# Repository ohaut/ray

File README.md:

# Ray module

The ray module is a 3-channel LED controller, designed to be
small, and built on the OHAUT framework.

OHAUT framework provides the common web interface, WiFi management,
connectivity to other smart devices (like Alexa , homeassistant, etc..),
as well as an update system which allows firmware to be published on
this repository (see [the gh-pages branch](https://github.com/ohaut/ray/tree/gh-pages/firmware/master) ),
long term it probably makes more sense to release via github releases of binaries.

The firmware code for this device is available in the [firmware](./firmware) directory.

The hardware design for this devices is available in the [hardware](./hardware) directory.

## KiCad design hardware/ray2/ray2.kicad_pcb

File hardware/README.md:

# Hardware design

This directory contains the hardware designs for the ray component.
All the designs are made using KiCad which is free and opensource
software, you can download it here: [www.kicad.org](https://www.kicad.org/)

* ray2: Is the latest version of the design, based on the RISC-V esp32c3
  chip from espressif, with embedded 4MB flash.

* microdimmer: Is a small footprint version, based on ESP8266, using SMD
  components and a DC/DC regulator.

* base_prototype: This was the initial protpotype, based on ESP8266, using
  insertion components on a 2-layer PCB.

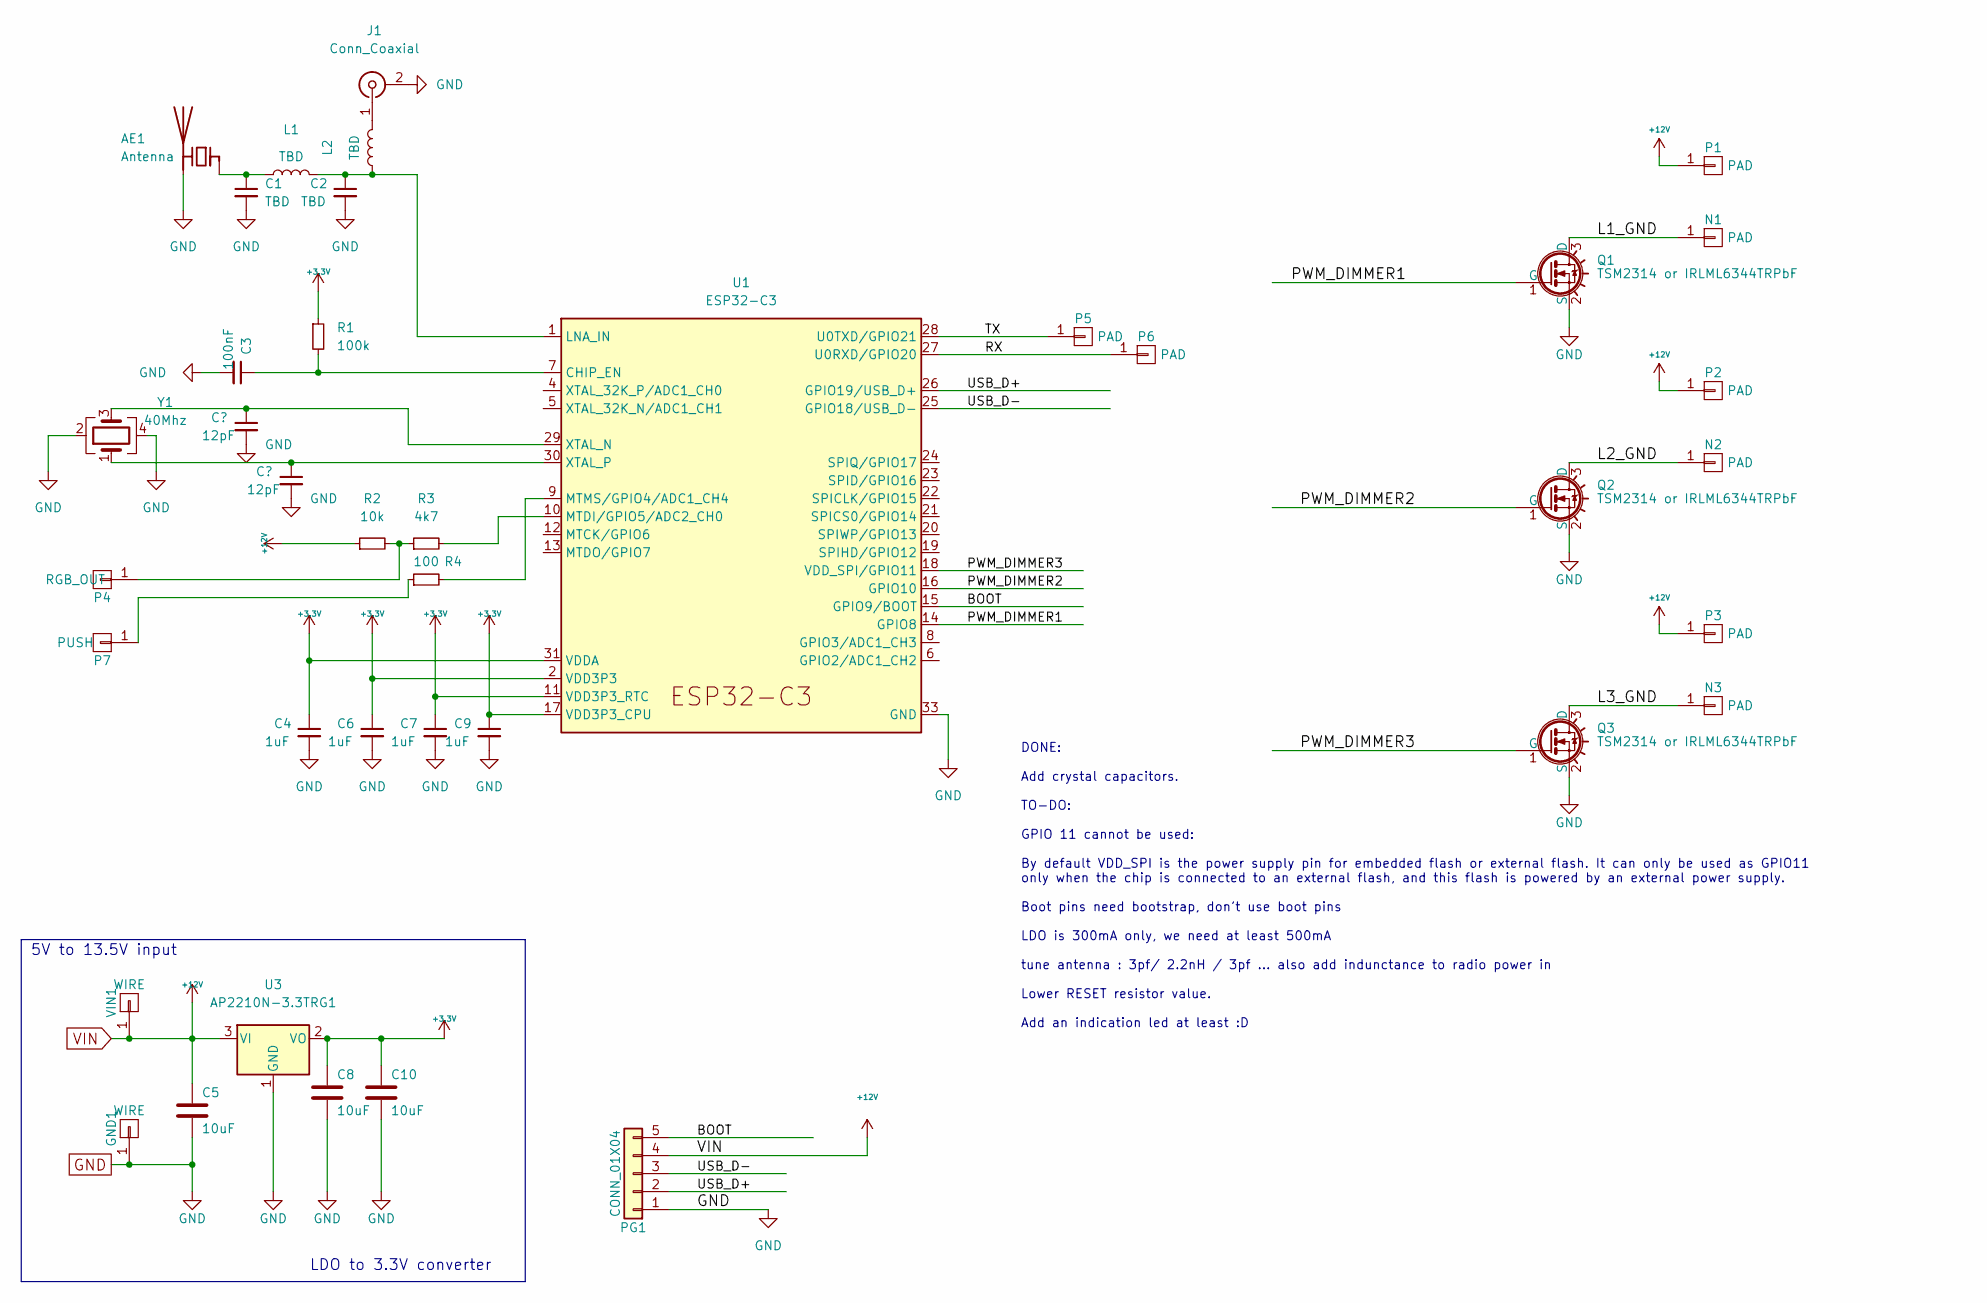
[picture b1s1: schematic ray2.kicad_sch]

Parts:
AE1: Antenna; Texas_SWRA117D_2.4GHz_Left
C1, C2: TBD; C_0402_1005Metric
C3: 100nF; C_0402_1005Metric
C4, C6, C7, C9: 1uF; C_0402_1005Metric
C5, C8, C10: 10uF; C_0603_1608Metric
GND1: WIRE; SolderWire-1.5sqmm_1x01_D1.7mm_OD3.9mm
J1: Conn_Coaxial; coaxial_u.fl-r-smt-1
L1, L2: TBD; L_0402_1005Metric
N1, N2, N3: PAD; SolderWire-0.5sqmm_1x01_D0.9mm_OD2.1mm
P1, P2, P3: PAD; SolderWire-0.5sqmm_1x01_D0.9mm_OD2.1mm
P4: RGB_OUT; SolderWire-0.5sqmm_1x01_D0.9mm_OD2.1mm
P5, P6: PAD; SolderWirePad_1x01_SMD_1x2mm
P7: PUSH; SolderWire-0.5sqmm_1x01_D0.9mm_OD2.1mm
PG1: CONN_01X04; PinHeader_1x05_P1.27mm_Vertical
Q1, Q2, Q3: TSM2314 or IRLML6344TRPbF; SOT-23
R1: 100k; R_0402_1005Metric
R2: 10k; R_0402_1005Metric
R3: 4k7; R_0402_1005Metric
R4: 100; R_0402_1005Metric
U1: ESP32-C3; QFN-32-1EP_5x5mm_P0.5mm_EP3.45x3.45mm
U3: AP2210N-3.3TRG1; SOT-23
VIN1: WIRE; SolderWire-1.5sqmm_1x01_D1.7mm_OD3.9mm
Y1: 40Mhz; Crystal_SMD_2520-4Pin_2.5x2.0mm

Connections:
+3V3: C4.1, C6.1, C7.1, C8.1, C9.1, C10.1, R1.1, U1.2 (VDD3P3), U1.3 (VDD3P3), U1.11 (VDD3P3_RTC), U1.17 (VDD3P3_CPU), U1.31 (VDDA), U1.32 (VDDA), U3.2 (VO)
/BOOT: PG1.5, U1.15 (GPIO9/BOOT)
/L1_GND: N1.1, Q1.3 (D)
/L2_GND: N2.1, Q2.3 (D)
/L3_GND: N3.1, Q3.3 (D)
/PWM_DIMMER1: Q1.1 (G), U1.14 (GPIO8)
/PWM_DIMMER2: Q2.1 (G), U1.16 (GPIO10)
/PWM_DIMMER3: Q3.1 (G), U1.18 (VDD_SPI/GPIO11)
/RX: P6.1, U1.27 (U0RXD/GPIO20)
/TX: P5.1, U1.28 (U0TXD/GPIO21)
/USB_D+: PG1.2, U1.26 (GPIO19/USB_D+)
/USB_D-: PG1.3, U1.25 (GPIO18/USB_D-)
GND: AE1.2 (PCB_Trace), C1.2, C2.2, C3.2, C4.2, C5.2, C6.2, C7.2, C8.2, C9.2, C10.2, GND1.1, J1.2 (Ext), PG1.1, Q1.2 (S), Q2.2 (S), Q3.2 (S), U1.33 (GND), U3.1 (GND), Y1.2, Y1.4
unnamed: AE1.1 (FEED), C1.1, L1.1
unnamed: C2.1, L1.2, L2.1, U1.1 (LNA_IN)
unnamed: C3.1, R1.2, U1.7 (CHIP_EN)
unnamed: J1.1 (In), L2.2
unnamed: P4.1, R2.2, R3.1
unnamed: P7.1, R4.1
unnamed: R3.2, U1.10 (MTDI/GPIO5/ADC2_CH0)
unnamed: R4.2, U1.9 (MTMS/GPIO4/ADC1_CH4)
unnamed: U1.29 (XTAL_N), Y1.3
unnamed: U1.30 (XTAL_P), Y1.1
VIN: C5.1, P1.1, P2.1, P3.1, PG1.4, R2.1, U3.3 (VI), VIN1.1

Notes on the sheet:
LDO to 3.3V converter
5V to 13.5V input
DONE: Add crystal capacitors. TO-DO: GPIO 11 cannot be used: By default VDD_SPI is the power supply pin for embedded flash or external flash. It can only be used as GPIO11 only when the chip is connected to an external flash, and this flash is powered by an external power supply. Boot pins need boo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

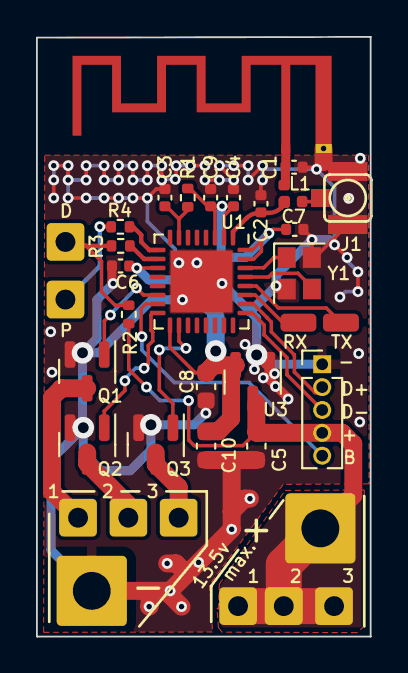
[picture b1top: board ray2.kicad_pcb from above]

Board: 2 copper layers, 18.5 x 33.3 mm, 37 parts (0 on the bottom side), 24 nets.

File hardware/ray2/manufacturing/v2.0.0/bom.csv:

"Id";"Designator";"Package";"Quantity";"Designation";"Supplier and ref";
1;"C10,C5,C8";"C_0603_1608Metric";3;"10uF";;;
2;"P2,P1,N3,N2,N1,P3";"SolderWire-0.5sqmm_1x01_D0.9mm_OD2.1mm";6;"PAD";;;
3;"R4";"R_0402_1005Metric";1;"100";;;
4;"C2,C1";"C_0402_1005Metric";2;"TBD";;;
5;"C7,C4,C6,C9";"C_0402_1005Metric";4;"1uF";;;
6;"Q1,Q2,Q3";"SOT-23";3;"TSM2314 or IRLML6344TRPbF";;;
7;"P6,P5";"SolderWirePad_1x01_SMD_1x2mm";2;"PAD";;;
8;"J1";"coaxial_u.fl-r-smt-1";1;"Conn_Coaxial";;;
9;"PG1";"PinHeader_1x05_P1.27mm_Vertical";1;"CONN_01X04";;;
10;"Y1";"Crystal_SMD_2520-4Pin_2.5x2.0mm";1;"40Mhz";;;
11;"VIN1,GND1";"SolderWire-1.5sqmm_1x01_D1.7mm_OD3.9mm";2;"WIRE";;;
12;"R2";"R_0402_1005Metric";1;"10k";;;
13;"C3";"C_0402_1005Metric";1;"100nF";;;
14;"U1";"QFN-32-1EP_5x5mm_P0.5mm_EP3.45x3.45mm";1;"ESP32-C3";;;
15;"R3";"R_0402_1005Metric";1;"4k7";;;
16;"P7";"SolderWire-0.5sqmm_1x01_D0.9mm_OD2.1mm";1;"PUSH";;;
17;"L1,L2";"L_0402_1005Metric";2;"TBD";;;
18;"R1";"R_0402_1005Metric";1;"100k";;;
19;"AE1";"Texas_SWRA117D_2.4GHz_Left";1;"Antenna";;;
20;"U3";"SOT-23";1;"AP2210N-3.3TRG1";;;
21;"P4";"SolderWire-0.5sqmm_1x01_D0.9mm_OD2.1mm";1;"RGB_OUT";;;

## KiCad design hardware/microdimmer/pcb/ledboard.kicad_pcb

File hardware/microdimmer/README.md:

base prototype IOT LED controller
=================================

3 channel led controller based on the ESP12-E, this is an opensource
piece of hardware meant to control 3 LED channels, and to integrate with
[openhab][2] via [mqtt][2] protocol.

[1]: http://www.openhab.org
[2]: http://mqtt.org

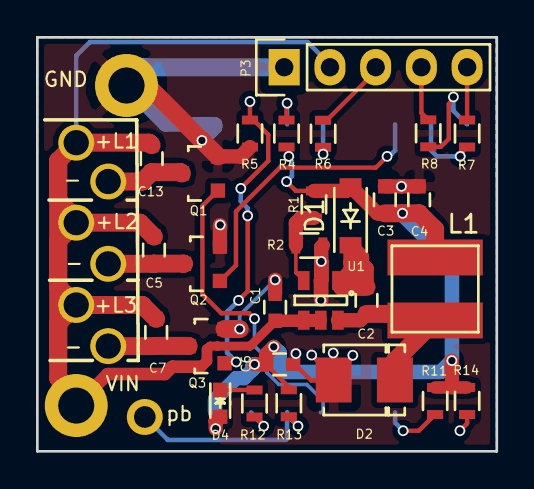
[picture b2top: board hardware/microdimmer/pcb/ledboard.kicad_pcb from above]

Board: 2 copper layers, 25.5 x 23.0 mm, 38 parts (1 on the bottom side), 24 nets.

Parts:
C1, C3, C4: 10uF; C_0603
C2, C5, C7, C13: 100nF; C_0603
C6: 2.2uF; C_0603
D1: 1N4148 SMD; SOD-123
D2: SS14; DO-214BA
D4: LED; LED-0603
L1: 15uH (744042150); L_1919
P1, P2: CONN_01X01; SolderWirePad_single_1-2mmDrill
P3: CONN_01X05; Pin_Header_Straight_1x05
P4, P5, P6, P7, P8, P9, P10: PAD; SolderWirePad_single_0-8mmDrill
Q1, Q2, Q3: TSM2314 or IRLML6344TRPbF; SOT-23
R1: 31.6K 1%; R_0603
R2: 10K 1%; R_0603
R4, R5, R6, R11, R13, R14: 10K; R_0603
R7, R8: 100; R_0603
R12: 470; R_0603
U1: MCP16301; SOT-23-6
U2: ESP-12E

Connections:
+3V3: C3.1, C4.1, C6.2, D1.2, D4.2, L1.2, R1.2, R4.1, R11.2, R13.1, R14.1, U2.8
/BOOT_MODE: R4.2, U2.17
/CHIP_ENABLE: R14.2, U2.3
/DC_BOOST: C2.1, D1.1, U1.1
/DC_FEEDBACK: R1.1, R2.2, U1.3
/DC_SW: C2.2, D2.1, L1.1, U1.6
/FLASH: P3.3, R6.1
/L1_GND: C13.2, P5.1, Q1.3
/L2_GND: C5.2, P7.1, Q2.3
/L3_GND: C7.2, P9.1, Q3.3
/PWM_DIMMER1: Q1.1, U2.5
/PWM_DIMMER2: Q2.1, U2.20
/PWM_DIMMER3: Q3.1, R5.2, U2.16
/RXD: P3.5, R7.1
/TXD: P3.4, R8.1
/_FLASH: R6.2, U2.18
/_RXD: R7.2, U2.21
/_TXD: R8.2, U2.22
/nLED: R12.2, U2.7
/nPUSHBUTTON: P10.1, R13.2, U2.6
/nRESET: R11.1, U2.1
GND: C1.2, C3.2, C4.2, C6.1, D2.2, P2.1, P3.1, Q1.2, Q2.2, Q3.2, R2.1, R5.1, U1.2, U2.15
unnamed: D4.1, R12.1
VIN: C1.1, C5.1, C7.1, C13.1, P1.1, P3.2, P4.1, P6.1, P8.1, U1.4, U1.5

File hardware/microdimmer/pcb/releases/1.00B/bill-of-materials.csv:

Id;Designator;Package;Quantity;Designation;Supplier and ref
1;U2;ESP-12E;1;ESP-12E;
2;C1,C3,C4;C_0603;3;10uF;
3;C2,C5,C7,C13;C_0603;4;100nF;
4;C6;C_0603;1;2.2uF;
5;D4;LED-0603;1;Orange LED;
6;L1;L_1919;1;15uH >0.6A (744042150);
8;Q1,Q2,Q3;SOT-23;3;TSM2314 or IRLML6344TRPbF;
9;R1;R_0603;1;31.6K 1%;
10;R2;R_0603;1;10K 1%;
11;R4,R5,R6,R11,R13,R14;R_0603;6;10K;
12;R7,R8;R_0603;2;100;
13;R12;R_0603;1;470;
14;U1;SOT-23-6;1;MCP16301;
18;D1;SOD-123;1;1N4148 SMD;
19;D2;DO-214BA;1;SS14;

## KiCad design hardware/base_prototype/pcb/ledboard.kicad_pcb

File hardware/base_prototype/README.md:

base prototype IOT LED controller
=================================

3 channel led controller based on the ESP12-E, this is an opensource
piece of hardware meant to control 3 LED channels, and to integrate with
[openhab][2] via [mqtt][2] protocol.

This module is a big version, meant to serve as SDK or handling
higher currents.

[1]: http://www.openhab.org
[2]: http://mqtt.org

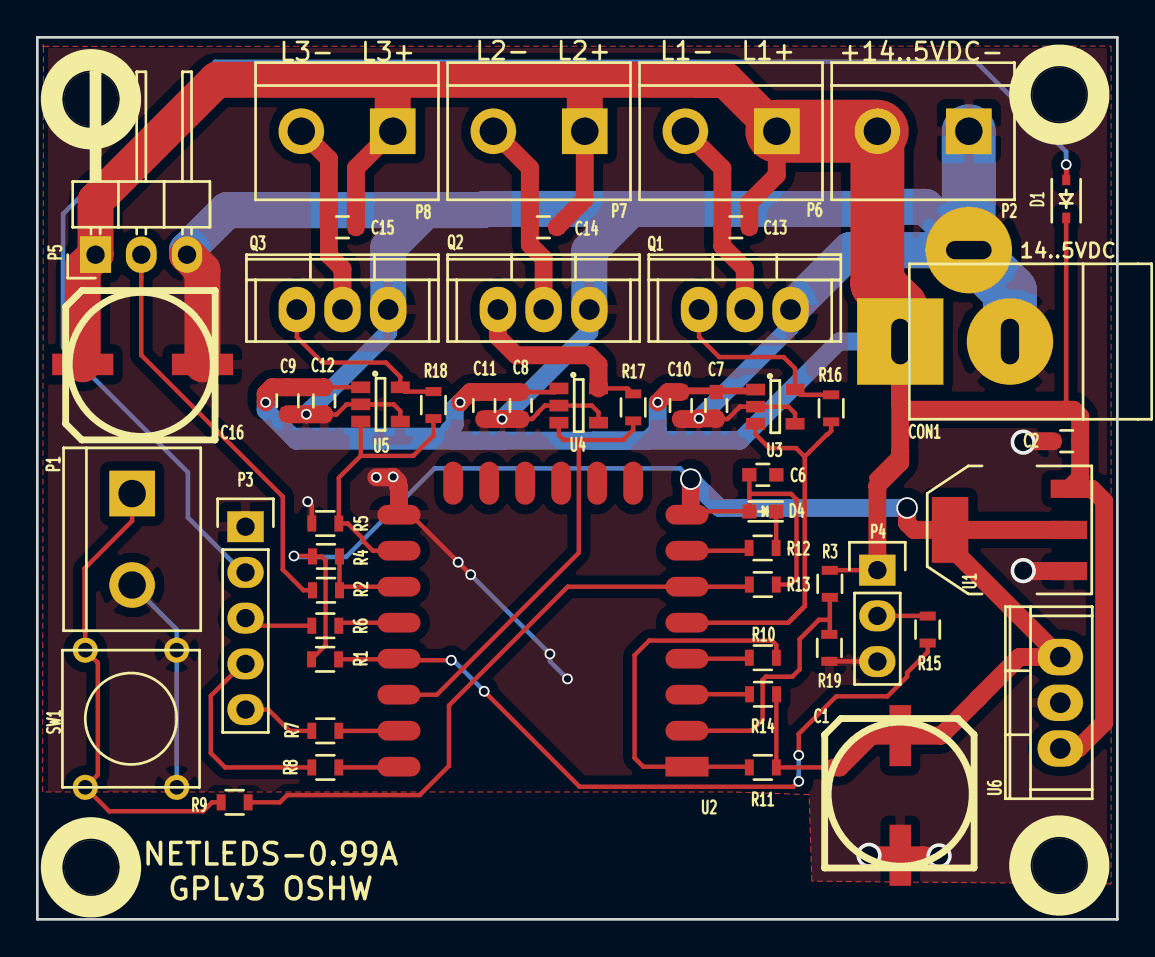
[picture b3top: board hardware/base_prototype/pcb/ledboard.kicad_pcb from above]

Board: 2 copper layers, 60.0 x 49.0 mm, 57 parts (0 on the bottom side), 31 nets.

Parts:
C1: 150uF 5V; SMD Capacitor Case F
C2, C6, C10, C11, C12: 4.7uF; C_0603
C7, C8, C9, C13, C14, C15: 100nF; C_0603
C16: 150uF 25V; SMD Capacitor Case F
CON1: BARREL_JACK; JACK_ALIM
D1: 1N4148 SMD 500mA SOD-123; SOD-323
D4: LED; LED-0603
P1, P2, P6, P7, P8: CONN_2; bornier2
P3: CONN_01X05; Pin_Header_Straight_1x05
P4: PIR SENSOR; Pin_Header_Straight_1x03
P5: CONN_01X03; Pin_Header_Angled_1x03
Q1, Q2, Q3: IRF540N; TO-220
R1, R4, R5, R6, R11, R13, R14: 10K; R_0603
R2, R7, R8, R9, R10, R15: 100; R_0603
R3: 15K; R_0603
R12: 470; R_0603
R16, R17, R18: NC 160; R_0603
R19: 1K; R_0603
SW1: SW_PUSH; SW_PUSH_SMALL
U1: LM1117-3.3; SOT-223
U2: ESP-12E
U3, U4, U5: FAN3100TSX; SOT-23-5
U6: NC R-78E3.3-0.5; TO-220
Z1, Z2, Z3, Z4: MHOLE; MHOLE_3MM

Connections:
+3V3: C1.1, C6.2, D4.2, R1.1, R4.1, R11.2, R13.1, R14.1, U1.2, U1.4, U2.8, U6.3
+12V: C2.2, C7.2, C8.2, C9.2, C10.2, C11.2, C12.2, C13.2, C14.2, C15.2, C16.1, CON1.1, D1.1, P2.2, P4.1, P5.1, P6.1, P7.1, P8.1, R3.1, U1.3, U3.1, U4.1, U5.1, U6.1
/CHIP_ENABLE: R14.2, U2.3
/FLASH: P3.3, R6.1
/PIR_MOTION: R1.2, R15.2, U2.19
/PWM_DIMMER1: R16.2, U2.5, U3.3
/PWM_DIMMER2: R17.2, U2.20, U4.3
/PWM_DIMMER3: R5.2, R18.2, U2.16, U5.3
/RXD: P3.5, R7.1
/TXD: P3.4, R8.1
/VIN: D1.2, P3.2
/VIN_DIV: R3.2, R19.1, U2.2
/WAKEUP_RST: R10.2, U2.4
/WS23812B_DO: R2.2, R4.2, U2.17
/_FLASH: R6.2, U2.18
/_PIR_MOTION: P4.2, R15.1
/_PWM_DIMMER1: Q1.1, R16.1, U3.5
/_PWM_DIMMER2: Q2.1, R17.1, U4.5
/_PWM_DIMMER3: Q3.1, R18.1, U5.5
/_RXD: R7.2, U2.21
/_TXD: R8.2, U2.22
/_WS2812B_DO: P5.2, R2.1
/nLED: R12.2, U2.7
/nPUSHBUTTON: R9.2, R13.2, U2.6
/nRESET: R10.1, R11.1, U2.1
AGND: C1.2, C2.1, C6.1, C7.1, C8.1, C9.1, C10.1, C11.1, C12.1, C16.2, CON1.2, CON1.3, P1.2, P2.1, P3.1, P4.3, P5.3, Q1.3, Q2.3, Q3.3, R5.1, R19.2, SW1.1, U1.1, U2.15, U3.2, U3.4, U4.2, U4.4, U5.2, U5.4, U6.2
unnamed: C13.1, P6.2, Q1.2
unnamed: C14.1, P7.2, Q2.2
unnamed: C15.1, P8.2, Q3.2
unnamed: D4.1, R12.1
unnamed: P1.1, R9.1, SW1.2

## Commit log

2015-09-27 Working version with 3 channels
2015-11-18 Add hardware pieces, and base arduino code.
2015-11-19 Soft light transitioning
2015-11-19 Ability to update via /setLed HTTP and reset on config.
2015-11-24 Allow multiple boot values for the dimmers
2015-11-24 Deprecate the lua version
2015-11-25 Do not expose an access point unless we're unable to connect.
2015-11-25 Create an unique AP SSID and MQTT ID by default
2015-11-25 Reorganized directory structure
2015-11-29 Cleanup and refactor of mqtt and HTTP API handling
2015-12-03 Version 1.00B of the PCB released.
    - Increased hole sizes for wire soldering
    - Fixed the diodes direction (they were inverted)
2015-12-11 Added PubSubClient library in the project.
    from https://github.com/knolleary/pubsubclient
    These bits are a library, and licensed as MIT, but
    included just to make compilation simpler and more
    stable by removing the external dependency.
2015-12-12 ConfigMap cleanups.
    Added foreach to ConfigMap.
    Moved a few functions from ConfigServer to ConfigMap:
    - writeTSV
    - readTSV
    - replaceVars
2015-12-12 Added platformio settings, and move PubSubClient back as lib.
2015-12-12 Renamed project to ray.
    It was clashing with particle.io photon.
2015-12-14 Add missing parameters to default configuration.
2015-12-15 Moved into ray directory for Arduino env compatibility.
2015-12-15 Platformio and Arduino compatibility
2016-01-04 Split out the mode specific settings.
    Lamp settings moved out to ConfigServerLamp, and a selector
    for new modes introduced (Greenhouse & Lamp).
    This change is still untested, it just compiles.
2016-01-18 Fix config server post address for connection config
2016-01-19 Fix race condition at start with default value.
    Fix race condition between default setting and MQTT
    stored setting at boot.
    Refactor the MQTT interface a bit, now we subscribe to all
    the device path, instead of led by led.
2016-03-06 Static file serving and Arduino >1.6.5 workaround.
    * Included static file serving and basic bootstrap design
    * Added rat_global_defs.h for Arduino >1.6.5 function discovery
    bug compatibility
    * Fixed a WiFi bug that made the AP mode unreliable: you should
    not call WiFi.begin() in AP mode, or it will intermitently
    disconnect the AP.
2016-03-06 Add SPIFS-less support for static serving of files.
    The included spifless.py tool takes the data/ directory and
    builds a data.h file with all the filesystem as constants.
    A ConstReader class is provided to allow streaming of the
    flash constants.
2016-03-06 Blink led on OTA update progress.
2016-03-07 SPIFLESS conditional
2016-03-08 firmwares
2016-03-08 No Jekyll mode to allow symlinks
2016-03-08 Introduce HTTP updates from github and SPIFFS versioning.
2016-03-08 Updated to version 000002, from source commit f7b3cd3
2016-03-08 Updated to version 000002, from source commit c25fec8
2016-03-08 publishbin.sh tool
2016-03-08 Updated to version 000002, from source commit b2a3f0d
2016-03-11 Moving to the spiffs html interface, and update support.
    Releaseing version 0000003
    The interface is being refactored into html+javascript+json,
    making the server side lighter, and the client side nicer.
    Files are stored in SPIFFS, and we use bootstrap + jquery.
    Binary updates are hosted via github.io webpages, and are
    published via the publishbin.sh tool.
2016-03-11 Updated to version 000003, from source commit 9aa7408
2016-03-11 Updated to version 000004, from source commit 7c8d4a0
2016-03-11 Extracted javascript to a separate file.
    Released version 000004
2016-03-11 Remove 000004
2016-03-11 Updated to version 000004, from source commit 54cb528
2016-03-12 Using inliner to reduce the number of requests
    Released Version 000005
2016-03-12 Updated to version 000005, from source commit 1328fb4
2016-03-12 Reduced the bootstrap features
2016-03-12 Disable webserver during upgrades.
    This way we can make sure upgrades are happening (connection refused),
    and requests don't disturb the looping stack for Arduino style,
    otherwise, http requests during upgrade not only were not served, but
    also made the upgrade likely to fail.
2016-03-12 Updated to version 000006, from source commit e573eb0
2016-03-12 Update progress dialog and JS logic
    Released Version 000007
2016-03-12 Updated to version 000007, from source commit 6e9b324
2016-03-12 Fix progress bar startup on firmware updates.
    Releases Version 000008
2016-03-12 Updated to version 000008, from source commit 140c1e3
2016-03-12 Fix update click to prevent following link.
    Release Version 000009
2016-03-12 Updated to version 000009, from source commit 7bc66e6
2016-03-13 Bootstrap without icons
2016-03-13 Instead of spiffs, download app.html.gz, lighter, and safer
2016-03-13 Updated to version 000010, from source commit a754cdf
2016-03-13 Proper app.html.gz download support
2016-03-13 Updated to version 000011, from source commit c9fbd5b
2016-03-14 Rearranged CSV format for html app versioning too
2016-03-14 Updated to version 000011, from source commit be948b6
2016-03-14 Updated to version 000012, from source commit 3334785
2016-03-14 Updated to version 000013, from source commit f692403
2016-03-14 Check html app version too.
2016-03-14 Updated to FW/APP 000014/000003, from source commit 8a17657
2016-03-14 Updated to FW/APP 000014/000004, from source commit 8a84f22
2016-03-14 Fix server restauration after update
2016-03-14 Updated to FW/APP 000015/000004, from source commit a2995eb
2016-03-14 simple version.js bump for test
2016-03-14 Updated to FW/APP 000015/000005, from source commit 714b81c
2016-03-15 Updated to FW/APP 000016/000005, from source commit 9568f12
2016-03-15 Cleanup
2016-03-16 Refactor config server and initial modal dialog.
    Refactor config server, and keep a minimal form to setup
    wifi if html APP is not installed.
    Move out the static server details to StaticServer.ino
    Provide an initial modal dialog until configuration is
    fetched from the device.
2016-03-16 Updated to FW/APP 000017/000006, from source commit 8b2838b
2016-03-16 Added a bindiff & binpatch tool to make binary diffs.
    Works better than compression, by reducing data downloads
    an average of 90% for single version jump updates.
    binpatching requires almost no memory compared to
    typical decompression.
2016-03-17 Add a slider for channel 0 in html.
2016-03-17 Use struct.pack for header in bindiff.py
2016-03-18 HTTP Update server for the app.html.gz
    You can now upload the app.html.gz via http post on browser, or via
    cmdline curl, which is quite useful in development.
    tools/prep_and_upload.sh accepts an IP address to prepare data_raw
    into app.html.gz, and upload to the device.
2016-03-18 Three sliders, instead of just one.
2016-03-18 Fix Update page html
2016-03-18 Updated to FW/APP 000018/000007, from source commit 87bca98
2016-03-20 Fix a bug where the sliders didn't update the lamps
2016-03-20 Updated to FW/APP 000018/000008, from source commit bf6992f
2016-03-20 Now dimmer values are loaded at startup
2016-03-20 Updated to FW/APP 000019/000009, from source commit d2a57df
2016-03-28 SSDP discovery support
2016-03-28 Updated to FW/APP 000020/000009, from source commit 8b748bb
2016-04-02 OHAUT integration via MQTT publishing
2016-04-02 Updated to FW/APP 000021/000010, from source commit 7cabe69
2016-09-22 Fix compilation issue
2016-09-29 Split javascript in common ohaut.js and ray.js
    This is a patch in a series where I will be splitting
    the main html & style bits to a separate repository
    to be pulled as git module.
2016-10-09 Transition to OHAUTlib
2016-10-09 Use the ohaut_lib framework to generate the JS/HTML
2016-10-09 Updated to FW/APP 000022/000011, from source commit a1dea76
2016-10-09 The device name is used to update via web
2016-10-09 Updated to FW/APP 000023/000011, from source commit 9e404ef
2016-10-11 Fix mqtt not working after OHAUTlib refactor
2016-10-14 Continue adoption of OHAUTservice
2016-10-16 Bump versions
2016-10-16 Updated to FW/APP 000024/000012, from source commit 30bc223
2016-10-16 check_updates requires the project as parameter
2016-10-16 Updated to FW/APP 000025/000013, from source commit 6f07556
2016-10-16 Use new mqtt publish parameter
2020-05-10 Update to alexa support plus no MQTT
2020-05-10 Webapp template
2020-05-10 Fix publish bin
2020-05-10 Updated to FW/APP 000026/000014, from source commit 1ed19e8
2020-05-12 Support ESP32 and OHAUTlib 0.2.1
2020-05-16 Add support for all global channel
2020-05-16 Update release scripts
2020-05-16 update ohautlib version
2020-05-16 Updated to FW/APP 000027/000015, from source commit bc016ff
2023-02-01 Updates for esp32c3
2023-02-04 Update python3 and add esp32c3 support
2023-02-04 Bump version with support for esp32c3
2023-02-04 Updated to FW/APP 000028/000015, from source commit 08f0e9c
2023-02-04 Partitions esp32c3
2023-02-05 Bump webapp for new ohaut domain
    Update to new ohaut domain
2023-02-05 Bump firmware version
2023-02-05 Fix publishbin script
2023-02-05 Updated to FW/APP 000029/000016, from source commit a61695b
2023-02-05 Add hardware design
2023-02-05 Use ohaut_lib from github
2023-02-05 Move firmware one level up
2023-02-05 Create push github action to build firmware
    Minimal CI
2023-02-05 Update push.yml
    Fix 2nd target
2023-02-05 Interface for switch/push button startup

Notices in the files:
hardware/base_prototype/pcb/ledboard.kicad_pcb:
GPLv3 OSHW
